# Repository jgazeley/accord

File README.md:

# Accord

Raspberry Pi Pico W firmware and keyless-entry hardware for a 2001 Honda Accord.

Two separate Pico W modules handle vehicle access and trip recording:

- **[Keyless entry](keyless/README.md)** — BLE commands, proximity-based
  lock/unlock, automatic relocking, and control of the trunk, lights and horn.
  Includes the KiCad schematic and PCB.
- **[Trip logger](logger/README.md)** — records speed/tachometer pulses,
  ignition, brake-warning and analog readings to an SD card, then uploads
  recordings over Wi-Fi during ignition-off windows.

Both run on the Pico W without an always-on in-car Linux computer. A Raspberry
Pi 4 serves as a portable development bench.

This is an ongoing vehicle-specific project. Build instructions, tests and
current limitations are documented with each module. The [logger server](logger/server/README.md) receives raw uploads and produces
trip JSON. Personal databases and dashboards are outside this repository.

## Development

This is the active home for Accord firmware, hardware and coordination.
See [current status](coordination/STATUS.md) and
[owner decisions](coordination/DECISIONS.md). Earlier experiments remain in
`accord-logger` as historical reference; useful missing material is migrated
selectively. Installed services and private data are separate from this source tree.

## License

Created by **Jayson Gazeley (jgazeley)**. Software and documentation use
[Apache 2.0](LICENSE); original hardware designs use
[CERN-OHL-P 2.0](keyless/hardware/LICENSE). Reuse, including commercial use,
is welcome with the notices required by those licenses preserved.
See [licensing and credit](LICENSING.md) for attribution and third-party terms.

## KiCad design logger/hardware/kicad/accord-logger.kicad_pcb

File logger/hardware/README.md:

# Logger hardware interface

The logger is a separate Pico W from the keyless module. The keyless KiCad
board in this repository is not a logger PCB. The current logger uses a
prototype signal-conditioning circuit, SD storage and an external regulated
5 V supply; the Pi is only a flashing and observation bench.

| Measurement/interface | Pico GPIO |
|---|---|
| Vehicle speed pulses | GP2 |
| Tachometer pulses | GP3 |
| Brake-warning level | GP4 |
| Conditioned ignition input | GP5 |
| Fuel analog input | GP26 / ADC0 |
| Supply analog input | GP27 / ADC1 |
| SD MISO / CS / SCK / MOSI | GP16 / GP17 / GP18 / GP19 |

This map comes from `accord-logger.ino` and `logger_sd.cpp`. Automotive
signals require the appropriate conditioning before reaching the Pico; this
pin map alone is not a wiring schematic. The brake-warning signal can represent
parking brake or low fluid, not an unambiguous parking-brake state. The fuel
input records ADC measurements, not an independently calibrated fuel quantity.

The **Rev A board design** is in [kicad/](kicad/) as `accord-logger.kicad_pro`:
complete schematic, 148-line BOM with every part footprinted, ERC clean, sized
for 80 × 120 mm. It includes the automatic power hold and cutoff, B2 input
isolation, the keyless RS-485 circuit, and one 10-pin Molex Mini-Fit Jr.
board connector. It is ready for the owner to place and route. It is **not
frozen and not fabrication-approved**: nothing has been built or bench tested.
The schematic is generated by `kicad/tools/gen_logger_sch.py`; see
[kicad/validation/COMMANDS.txt](kicad/validation/COMMANDS.txt). Engineering
record: [power/LAYOUT_CLOSURE.md](power/LAYOUT_CLOSURE.md); risks and bring-up
tests: [LRA12_HANDOFF.md](LRA12_HANDOFF.md). Automatic-power firmware exists
as an opt-in candidate; manual power remains the default.

The pin map above is the **as-built** firmware baseline. Rev A changes what
GP5 means and adds GP6; see [as-built/REV_A_INTERFACES.md](as-built/REV_A_INTERFACES.md) §1.

B2 input isolation (ASSR-601JV) is in the schematic; background in the
[B2 study](isolation/B2_ISOLATION.md) and [enable design](isolation/ISO_ENABLE.md).

Current electrical/PCB context: [Rev A context](REV_A_CONTEXT.md).
Current status: [STATUS.md](../../coordination/STATUS.md); owner decisions: [DECISIONS.md](../../coordination/DECISIONS.md).

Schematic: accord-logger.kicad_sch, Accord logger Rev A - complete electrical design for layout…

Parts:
BT1: BR2032; BatteryHolder_Keystone_3034_1x20mm
C1, C2: 1uF; C_0805_2012Metric_Pad1.18x1.45mm_HandSolder
C3: 1uF; C_Rect_L7.2mm_W5.5mm_P5.00mm_FKS2_FKP2_MKS2_MKP2
C4, C5, C6: 4.7uF/50V; C_1210_3225Metric_Pad1.33x2.70mm_HandSolder; MPN Murata GRM32ER71H475KA88L
C7, C17, C18, C19, C20, C21, C22, C23, C24, C25: 100nF; C_0805_2012Metric_Pad1.18x1.45mm_HandSolder
C8: 47uF/16V; CP_Radial_D6.3mm_P2.50mm
C9, C11: 100nF/100V; C_0805_2012Metric_Pad1.18x1.45mm_HandSolder
C10: 100uF/50V; CP_Radial_D8.0mm_P3.50mm; MPN Panasonic EEUFR1H101
C12: 10nF/50V; C_0805_2012Metric_Pad1.18x1.45mm_HandSolder
C13: 100nF/50V; C_0805_2012Metric_Pad1.18x1.45mm_HandSolder
C14: 1000uF/16V; CP_Radial_D10.0mm_P5.00mm; MPN Panasonic EEUFR1C102
C15: 33uF/16V; CP_Radial_Tantal_D6.0mm_P2.50mm; MPN KYOCERA AVX TAP336K016SCS
C16: 10nF; C_0805_2012Metric_Pad1.18x1.45mm_HandSolder
D101, D102, D103, D104, D105, D106, D107, D109: 1N5819; D_DO-41_SOD81_P5.08mm_Vertical_AnodeUp; MPN Diodes Inc 1N5819HW-7-F
D108, D113: 1.5KE20A-E3/54; D_DO-201AD_P5.08mm_Vertical_KathodeUp; MPN Vishay 1.5KE20A-E3/54
D110: 1N4148W; D_SOD-123; MPN Diodes Inc 1N4148W-7-F
D111: BZX55C22; D_DO-35_SOD27_P2.54mm_Vertical_KathodeUp; MPN Vishay BZX55C22-TAP
D112, D115: SB360-E3/54; D_DO-201AD_P5.08mm_Vertical_AnodeUp; MPN Vishay SB360-E3/54
D114: BZX55C10; D_DO-35_SOD27_P2.54mm_Vertical_KathodeUp; MPN Vishay BZX55C10-TAP
D116: 1N4004-E3/54; D_DO-41_SOD81_P5.08mm_Vertical_KathodeUp; MPN Vishay 1N4004-E3/54
J1: Board connector 14-way; JAE_IL-AG5-14P-D3L2-A; MPN JAE IL-AG5-14P-D3L2-A, 14 contact right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
J3: Spare GP11-13 / switched power; PinHeader_2x03_P2.54mm_Vertical
J4: Reset RUN-GND; PinHeader_1x02_P2.54mm_Vertical
J5: SD breakout 6-way; PinHeader_1x06_P2.54mm_Vertical
JP1: HOLD link; PinHeader_1x02_P2.54mm_Vertical
JP2: TERM default OPEN; PinHeader_1x02_P2.54mm_Vertical
JP3: BIAS HI default OPEN; PinHeader_1x02_P2.54mm_Vertical
JP4: BIAS LO default OPEN; PinHeader_1x02_P2.54mm_Vertical
L1: 22uH; L_Radial_D8.7mm_P5.00mm_Fastron_07HCP; MPN Bourns RLB0912-220KL
Q1, Q9: MMBT3904; SOT-23; MPN onsemi MMBT3904LT1G
Q2, Q3, Q4, Q8: BSS138P; SOT-23; MPN Nexperia BSS138P
Q5: IPD50P04P4L-11; TO-252-3_TabPin2; MPN Infineon IPD50P04P4L11ATMA2
Q6, Q7: 2N3904; TO-92_Inline; MPN onsemi 2N3904
R1, R3, R5, R10, R16: 22k; R_Axial_DIN0204_L3.6mm_D1.6mm_P5.08mm_Horizontal
R2: 33k; R_Axial_DIN0204_L3.6mm_D1.6mm_P5.08mm_Horizontal
R4, R6: 6.8k; R_Axial_DIN0204_L3.6mm_D1.6mm_P5.08mm_Horizontal
R7: 7.5k; R_Axial_DIN0204_L3.6mm_D1.6mm_P5.08mm_Horizontal
R8, R11, R18: 4.7k; R_Axial_DIN0204_L3.6mm_D1.6mm_P5.08mm_Horizontal
R9, R12, R19, R24, R26, R29, R37, R38: 1k; R_Axial_DIN0204_L3.6mm_D1.6mm_P5.08mm_Horizontal
R13: 2.2k; R_Axial_DIN0414_L11.9mm_D4.5mm_P5.08mm_Vertical
R14, R28, R44: 47k; R_Axial_DIN0204_L3.6mm_D1.6mm_P5.08mm_Horizontal
R15: 220k; R_Axial_DIN0204_L3.6mm_D1.6mm_P5.08mm_Horizontal
R17, R20, R25, R27, R34, R35: 100k; R_Axial_DIN0204_L3.6mm_D1.6mm_P5.08mm_Horizontal
R21, R31, R36: 10k; R_Axial_DIN0204_L3.6mm_D1.6mm_P5.08mm_Horizontal
R22: 820R; R_Axial_DIN0204_L3.6mm_D1.6mm_P5.08mm_Horizontal
R23: 270R; R_Axial_DIN0204_L3.6mm_D1.6mm_P5.08mm_Horizontal
R30: 10k; R_Axial_DIN0207_L6.3mm_D2.5mm_P5.08mm_Vertical
R32: 1k; R_Axial_DIN0414_L11.9mm_D4.5mm_P5.08mm_Vertical
R33: 2.2k; R_Axial_DIN0204_L3.6mm_D1.6mm_P5.08mm_Horizontal
R39: 0R; R_0805_2012Metric_Pad1.20x1.40mm_HandSolder
R40: 0R; R_0805_2012Metric_Pad1.20x1.40mm_HandSolder; not fitted
R41, R43, R45, R46: 100k; R_0805_2012Metric_Pad1.20x1.40mm_HandSolder
R42: 1k; R_0805_2012Metric_Pad1.20x1.40mm_HandSolder
R47, R48: 390R; R_Axial_DIN0207_L6.3mm_D2.5mm_P5.08mm_Vertical
R49: 120R; R_Axial_DIN0207_L6.3mm_D2.5mm_P5.08mm_Vertical
R50, R51: 4.7k; R_0805_2012Metric_Pad1.20x1.40mm_HandSolder
R52: 10k; R_0805_2012Metric_Pad1.20x1.40mm_HandSolder
TP1, TP2, TP3, TP4, TP5, TP6, TP7, TP8, TP9, TP12, TP17, TP20: TestPoint; TestPoint_Pad_D2.0mm
TP21, TP22, TP23: TestPoint; TestPoint_Loop_D2.50mm_Drill1.0mm
U1: RaspberryPi_Pico_W; RaspberryPi_Pico_W_SMD_HandSolder; MPN Raspberry Pi Pico W (RP2040 + CYW43439)
U2: PC817; DIP-4_W7.62mm; MPN Sharp PC817XNNSZ1B or qualified equival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
U3: ASSR-601JV; ASSR-601Jx_SO-16-12Lead_11.634x10.363mm_P1.27mm; MPN Broadcom ASSR-601JV-000E
U4: TPS70950QDBVRQ1; SOT-23-5_HandSoldering; MPN TI TPS70950QDBVRQ1
U5: TPS3839K50DBZR; SOT-23; MPN TI TPS3839K50DBZR
U6: LM2678T-5.0; TO-220-7_P2.54x3.7mm_StaggerOdd_Lead3.8mm_Vertical; MPN TI LM2678T-5.0/NOPB
U7: OV-7604-C7-32.768KHZ-20PPM-TA-QC; Oscillator_SMD_MicroCrystal_OV-7604-C7_SON-4_3.2x1.5mm; MPN Micro Crystal OV-7604-C7-32.768KHZ-20PP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
U8: 74AHC1G17GV; SOT-353_SC-70-5_Handsoldering; MPN Nexperia 74AHC1G17GV
U9: SN74LVC1G97DBVR; SOT-23-6_Handsoldering; MPN TI SN74LVC1G97DBVR
U10: CD74HC4060M96; SOIC-16_3.9x9.9mm_P1.27mm; MPN TI CD74HC4060M96
U11: CD74HC4020M96; SOIC-16_3.9x9.9mm_P1.27mm; MPN TI CD74HC4020M96
U12: CD4011BM96; SOIC-14_3.9x8.7mm_P1.27mm; MPN TI CD4011BM96
U13: CD4071BM96; SOIC-14_3.9x8.7mm_P1.27mm; MPN TI CD4071BM96
U14: CD4093BM96; SOIC-14_3.9x8.7mm_P1.27mm; MPN TI CD4093BM96
U15: MAX3485; DIP-8_W7.62mm; MPN Analog Devices MAX3485EPA+
U16: DS3231SN; SOIC-16W_7.5x10.3mm_P1.27mm

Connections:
/A5: C5.1, C6.1, C7.1, C18.1, C19.1, C20.1, C21.1, C22.1, C23.1, R38.1, R46.2, TP9.1, U2.4, U4.5 (OUT), U5.3 (VDD), U9.5 (VCC), U10.16 (VDD), U11.16 (VDD), U12.14 (VDD), U13.14 (VDD), U14.2 (A2), U14.14 (VDD)
/AGND: C1.2, C2.2, D105.2 (A), D107.2 (A), J1.10, R8.2, R11.2, TP23.1, U1.33 (AGND)
/ARM: R42.1, U8.2, U9.6 (IN2), U12.3 (AY), U12.6 (B2)
/ARM_G: Q8.1 (G), R42.2, R43.1
/ARM_RESET: U13.11 (DY), U14.8 (C1), U14.9 (C2)
/B1_TAP: J1.4, R3.1
/B2_ISO: R1.1, U3.9 (D2), U3.10 (D2)
/B2_TAP: J1.3, U3.15 (D1), U3.16 (D1)
/B5: C13.1, C14.1, D116.2 (A), J3.1, L1.2, R23.1, R37.1, TP5.1, U6.6 (FEEDBACK)
/B11_TAP: D108.1 (A1), D109.2 (A), J1.5, R10.1
/BAD: R16.1, U13.1 (A1), U13.8 (C1), U14.4 (BY)
/BASE_RESET: U11.11 (MR), U13.3 (AY), U13.5 (B1)
/BATT_IN: D112.2 (A), J1.6
/BOOST: C12.2, U6.3 (BOOST)
/BRAKE_IN: D103.2 (A), R5.2, R6.1, U1.6 (GPIO4)
/BUS_DE: R30.1, U1.14 (GPIO10), U15.2 (~RE), U15.3 (DE)
/C11_TAP: J1.9, R7.1
/C14_TAP: J1.13, R5.1
/CLK32: U9.4 (Y), U10.11 (CLK)
/CLKOE: U7.3 (CLKOE), U8.4
/CNT_Q8: R40.1, U11.13 (Q8)
/CNT_Q13: R39.1, U11.2 (Q13)
/COUNT1_RESET: U10.12 (MR), U13.4 (BY)
/EXPIRED: R39.2, R40.2, R41.1, U13.9 (C2)
/FAULT_RESET: U13.10 (CY), U13.12 (D1)
/FUEL_ADC: C1.1, D104.2 (A), D105.1 (K), R9.2, U1.31 (GPIO26_ADC0)
/FUEL_DIV: R7.2, R8.1, R9.1
/GATE: D114.2 (A), Q5.1 (G), R31.2, R32.1, TP2.1
/HOLD_B: Q7.2 (B), R29.2, R35.1
/HOLD_JH: JP1.2 (B), R29.1
/HOLD_N: Q9.3 (C), R46.1, U13.13 (D2)
/HOLD_RAW: JP1.1 (A), R28.1, R44.1, U1.9 (GPIO6)
/IGN_A: R14.1, R15.1, U2.3
/IGN_B: Q6.2 (B), R33.2, R34.1
/IGN_LED_A: D110.1 (K), R13.2, U2.1
/IGN_POS: D109.1 (K), R13.1, R33.1
/IGN_Q: R19.1, U12.10 (CY), U13.2 (A2), U14.12 (D1)
/IGN_RC: C3.1, R15.2, R18.2, TP12.1, U14.1 (A1)
/ISO_EN: R24.1, TP20.1, U1.10 (GPIO7)
/ISO_EN_G: Q4.1 (G), R24.2, R25.1
/ISO_LED_A: R23.2, U3.4 (AN)
/ISO_LED_K: Q3.3 (D), U3.5 (CA)
/ISO_MID: Q3.2 (S), Q4.3 (D)
/ISO_PG_G: Q3.1 (G), R26.2, R27.1
/MON_B: Q9.1 (B), R44.2, R45.1
/NARM: U12.2 (A2), U12.4 (BY), U13.6 (B2)
/P3V3_SW: C8.1, C24.1, C25.1, D101.1 (K), D102.1 (K), D103.1 (K), D104.1 (K), D106.1 (K), J3.4, J5.1, JP3.1 (A), R21.1, R50.1, R51.1, R52.1, TP7.1, U1.36 (3V3), U15.8 (VCC), U16.2 (VCC)
/P12: C9.1, D112.1 (K), D113.1 (A1), D114.1 (K), Q5.3 (S), R22.1, R31.1, TP1.1
/PGND: BT1.2 (-), C3.2, C4.2, C5.2, C6.2, C7.2, C8.2, C9.2, C10.2, C11.2, C13.2, C14.2, C15.2, C16.2, C17.2, C18.2, C19.2, C20.2, C21.2, C22.2, C23.2, C24.2, C25.2, D108.2 (A2), D110.2 (A), D111.2 (A), D113.2 (A2), D115.2 (A), J1.2, J1.14, J3.2, J4.2, J5.2, JP4.2 (B), Q1.2 (E), Q2.2 (S), Q4.2 (S), Q6.1 (E), Q7.1 (E), Q9.2 (E), R2.2, R4.2, R6.2, R14.2, R17.2, R20.2, R25.2, R27.2, R28.2, R30.2, R34.2, R35.2, R36.2, R37.2, R41.2, R43.2, R45.2, TP21.1, TP22.1, U1.3 (GND), U1.8 (GND), U1.13 (GND), U1.18 (GND), U1.23 (GND), U1.28 (GND), U1.38 (GND), U2.2, U4.2 (GND), U5.1 (GND), U6.4 (GND), U7.2 (GND), U8.3 (GND), U9.1 (IN1), U9.2 (GND), U10.8 (VSS), U11.8 (VSS), U12.7 (VSS), U12.12 (D1), U12.13 (D2), U13.7 (VSS), U14.7 (VSS), U15.5 (GND), U16.5 (GND), U16.6 (GND), U16.7 (GND), U16.8 (GND), U16.9 (GND), U16.10 (GND), U16.11 (GND), U16.12 (GND), U16.13 (GND)
/PGOOD: R26.1, TP17.1, U5.2 (~RESET), U14.5 (B1), U14.6 (B2)
/P_AON: C4.1, D111.1 (K), R22.2, TP8.1, U4.1 (IN)
/QH_C: Q7.3 (C), Q8.2 (S)
/QUAL_N: U12.8 (C1), U12.9 (C2), U14.3 (AY)
/QUAL_N_REPORT: Q2.3 (D), R21.2, U1.7 (GPIO5)
/REP_G: Q2.1 (G), R19.2, R20.1
/RESET_N: U12.5 (B1), U14.10 (CY), U14.13 (D2)
/RS485_A: J1.1, R47.2, R49.1, U15.6 (A)
/RS485_B: J1.7, JP2.2 (B), R48.1, U15.7 (B)
/RS485_BIAS_HI: JP3.2 (B), R47.1
/RS485_BIAS_LO: JP4.1 (A), R48.2
/RS485_TERM: JP2.1 (A), R49.2
/RST_B: Q1.1 (B), R16.2, R17.1
/RST_C: Q1.3 (C), R18.1
/RTC_INT: R52.2, U1.29 (GPIO22), U16.3 (~INT/SQW)
/RTC_SCL: R51.2, U1.27 (GPIO21), U16.16 (SCL)
/RTC_SDA: R50.2, U1.26 (GPIO20), U16.15 (SDA)
/RTC_VBAT: BT1.1 (+), U16.14 (VBAT)
/RUN: J4.1, U1.30 (RUN)
/SD_CS: J5.4, U1.22 (GPIO17)
/SD_MISO: J5.3, U1.21 (GPIO16)
/SD_MOSI: J5.6, U1.25 (GPIO19)
/SD_SCK: J5.5, U1.24 (GPIO18)
/SET_N: U12.1 (A1), U14.11 (DY)
/SINK: Q6.3 (C), Q8.3 (D), R32.2
/SPARE_GP11: J3.6, U1.15 (GPIO11)
/SPARE_GP12: J3.5, U1.16 (GPIO12)
/SPARE_GP13: J3.3, U1.17 (GPIO13)
/SUPPLY_ADC: C2.1, D106.2 (A), D107.1 (K), R12.2, U1.32 (GPIO27_ADC1)
/SUPPLY_DIV: R10.2, R11.1, R12.1
/SW: C12.1, D115.1 (K), L1.1, TP4.1, U6.1 (SWITCH)
/TACH_IN: D102.2 (A), R3.2, R4.1, U1.5 (GPIO3)
/UART1_RX: U1.12 (GPIO9), U15.1 (RO)
/UART1_TX: U1.11 (GPIO8), U15.4 (DI)
/UCLK_Q14: U10.3 (Q14), U11.10 (CLK)
/VCLK: C15.1, C16.1, C17.1, R38.2, U7.4 (VDD), U8.5 (VCC)
/VIN_SW: C10.1, C11.1, Q5.2 (D), R36.1, TP3.1, U6.2 (VIN)
/VSS_IN: D101.2 (A), R1.2, R2.1, U1.4 (GPIO2)
/VSYS: D116.1 (K), TP6.1, U1.39 (VSYS)
/XO_OUT: U7.1 (CLKOUT), U9.3 (IN0)

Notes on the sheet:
TEST POINTS AND GROUND LOOPS - REV_A_INTERFACES S5.3, delta D8
Onboard switched power
X6 RESOLVED: QUALIFIED IGNITION, A5 DOMAIN - CUTOFF_MARGIN_REVIEW S2
Retain 1.5KE20A by choice, not because a 60 V low-leakage QP is absent. SQD50P06-15L has 50 uA max IDSS at 125 C and -60 V. The inherited 1.5KE30A screens 43.81 V at 85 C: 1.19 V below LM2678 absolute, 3.81 V above operating. It also requires a redesigned A5 clamp. Selected 1.5KE20A screens 29.20 V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
GP0/GP1, GP14/GP15 and GP28 are deliberately unconnected. GP20/GP21 are I2C0 SDA/SCL and GP22 INT/SQW for the DS3231 (D-RTC-14). GP7 is now ISO_EN, the B2 isolation enable, confirmed free in S1. GP8/GP9 (UART1) and GP10 (tied DE//RE) drive onboard RS-485. GP13 is offered on the trimmed J3 spare/pow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
The fitted cell returned the ignition LED cathode to the B16 cluster conductor with nothing in series, putting 4.7-5.8 mA of signal- dependent current through the node both ADC channels reference, which REV_A_INTERFACES S4 says must never become a power return. D5 and that return cannot both stand.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
Pico W pin map
The opto LED return - R06-REV-2 decided
What is still open - none of it a layout blocker
Vehicle inputs: one switch, four justified bypasses
Reuses the existing power candidate as DESIGN.md S3 lists it (D-POWER-02), with the reviewed deltas D7 and D13 and the LRA-02 component selections. The LM2678, its TVS role, bulk capacitors, boost cap, inductor value and both Schottky positions all have in-service precedent on the keyless board in 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
Independent cutoff - what it does and does not cover
HOLD driver and the cutoff path
PICO W - REV_A_INTERFACES S1 Rev A column
INDEPENDENT CLOCK BLOCK - CUTOFF_MARGIN_REVIEW S1
SD and expansion
SPI0 at 12 MHz on switched 3V3 only (GP16 MISO, GP17 CS, GP18 SCK, GP19 MOSI). D6 bulk is now a selected 47 uF: a 200 mA write spike for 1 ms inside 100 mV of droop needs 2 uF, so this is an order of margin without an oversized can. Any move of this module to a 5 V rail re-opens the MISO clearance 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
RS-485 - keyless circuit; bias and termination OPEN by default
ONBOARD SWITCHED POWER - power/DESIGN.md S3, deltas D7 and D13, X7 entry clamp resolved
X7 SECOND STAGE: ALWAYS-ON A5 SUPPLY AND SUPERVISOR - CUTOFF_MARGIN_REVIEW S3 + LAYOUT_CLOSURE S3
HOLD DRIVER - delta D2
Classified in full in LRA12_HANDOFF.md. In short: ORDER GATE ASSR-601JV availability (fallback AQY221N2S specified, strictly smaller, same keepout); capacitor approval-sheet bias/aging/IR data. BRING-UP A5 ground current below 100 uA load; hot leakage of QP, QI, QH, QMON, QS, QREPORT and the opto; 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
NOTES - LRA-12 electrical closure
Test points and ground loops
IGNITION OPTO CELL, VEHICLE SIDE - AS_BUILT S3.4; LED return moved to PGND
X1 ENABLE: GPIO PLUS HARDWARE PGOOD PERMISSION - LAYOUT_CLOSURE S4
Five fitted cells, carried forward with no value changed (AS_BUILT S2). B2 is the only branch energized with the key out - 4.669 V open circuit, 4.140 V loaded, drawing 140.8 uA of which 109.2 uA was being back-fed into the unpowered 3V3 rail through a forward-biased clamp. It gets the series switc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
LRA-12 - what changed, and the one thing to read first
Nominal 2048 s from qualified ignition loss, on its own always-on supply and its own clock. The Pico cannot refresh it with HOLD, resets, network traffic or watchdog servicing; releasing HOLD disarms it, and only a qualified ignition assertion can grant it again. Reset dominates set in the settled 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
X8 RESOLVED: INDEPENDENT MAXIMUM-ON CUTOFF, 2048 s - MAX_ON_CUTOFF
GP6 HOLD_RAW with a 47k external pulldown and the JH MAINTENANCE link. Firmware latches it LOW before output enable; 4 mA drive, 2.6 V loaded qualification target. QS is the series interruption the independent timer uses: drain to SINK, source to the QH collector, body diode blocking the sink direc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
VEHICLE INPUTS - AS_BUILT S2, ratios and clamps unchanged; B2 series isolation fitted, other four branches bypassed
This is the LRA-06 capture with its eight electrical placeholders resolved. Every populated part now carries a checked footprint and no dashed NOT SELECTED body remains. The decisions, their calculations and the residual gates are in power/LAYOUT_CLOSURE.md and LRA12_HANDOFF.md; read those before c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
Twenty-five test loops. Three separate ground loops follow the keyless pattern: buck, Pico and harness end, the last on the bonded B16/AGND sense node. J4 shorts RUN to GND for a reset without cutting power. TP_PAON is where the <=28 V protected-rail criterion is measured. TP_GATE against TP_P12 is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
Voltage envelope - LRA-12R decision
SPARE GP13 / SWITCHED POWER AND RESET
SD - AS_BUILT S3.5, delta D6
REAL-TIME CLOCK - DS3231 on the board (D-RTC-14)
DS3231SN# (TCXO, -40 to +85 C) on I2C0: GP20 SDA, GP21 SCL, GP22 INT/SQW. VCC and all three pull-ups on switched 3V3 only, so nothing feeds the Pico while it is off; the chip runs from the cell then (about 3 uA). Cell: BR2032 (rated to +85 C, a parked car exceeds CR2032 ratings) in a Keystone 3034 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

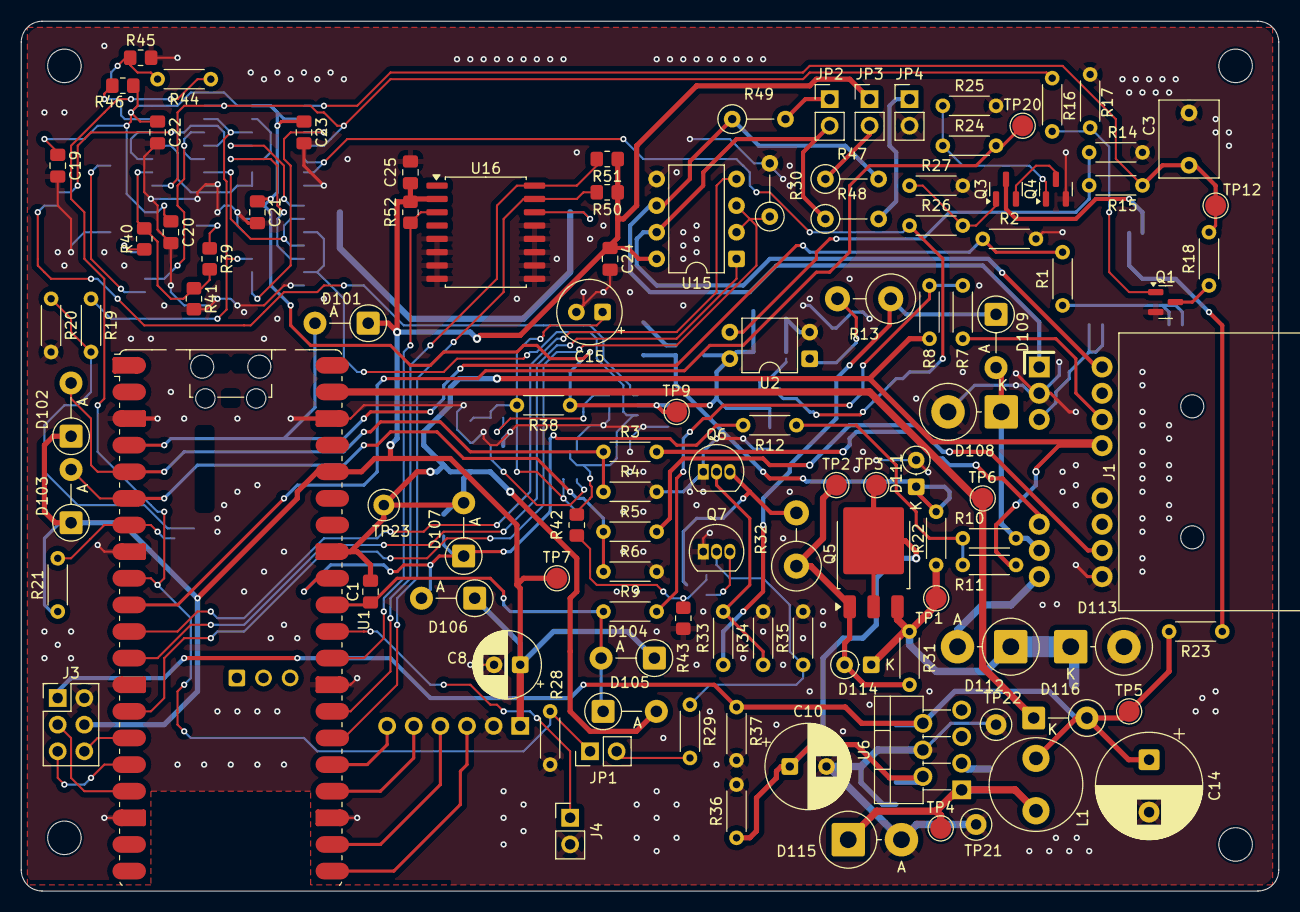
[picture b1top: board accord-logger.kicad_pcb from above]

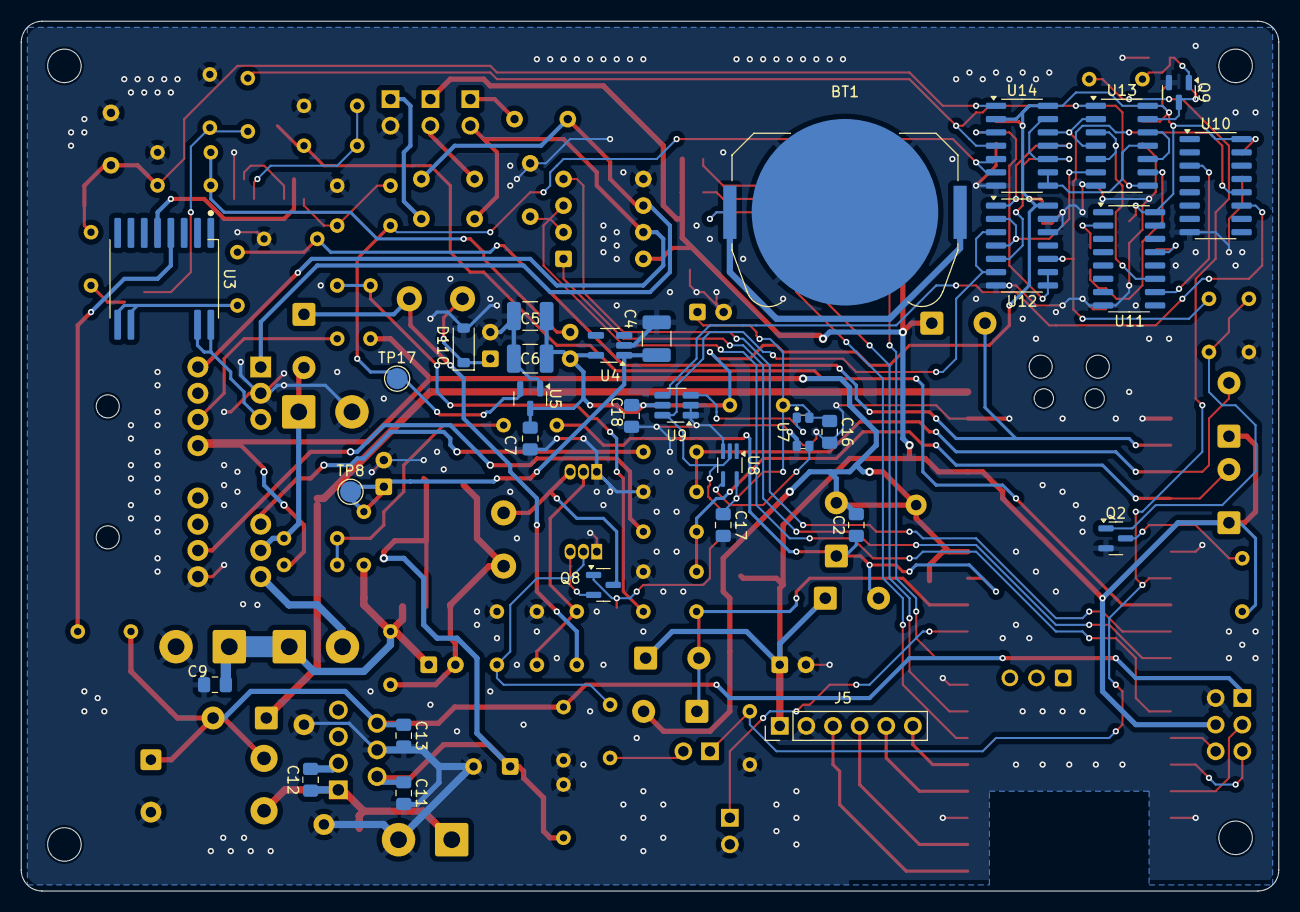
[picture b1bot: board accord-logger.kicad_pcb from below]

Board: 2 copper layers, 120.0 x 83.0 mm, 147 parts (31 on the bottom side), 89 nets.

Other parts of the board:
H1, H2, H3, H4: M3 mounting hole; MountingHole_3.2mm_M3

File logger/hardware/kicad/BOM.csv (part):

reference,source_designator,value,symbol,manufacturer_part_or_type,footprint,population,status,source,notes
J1,J1,Board connector 14-way,Connector_Generic:Conn_01x14,"JAE IL-AG5-14P-D3L2-A, 14 contact right-angle pin header",accord-logger:JAE_IL-AG5-14P-D3L2-A,FIT,SELECTED,DECISIONS D-CONN-06 / JAE IL-AG5 catalogue,"JAE IL-AG5 2.5 mm, 14 contacts, right-angle through-hole with board guides, 3 A per contact. Mates with housing IL-AG5-14S-D3C1-A and IL-AG5-C1-5000 crimp sockets (AWG 22-18); hand crimp tool CT150-1-AG5. Same family as the keyless 22P. Footprint pin numbers follow the keyless 22P convention (pin 1 outer row, left end from the mating face): verify against the housing cavity numbers before crimping. 6 BATT_IN, +12 V through the harness inline fuse (1 A, at the feed end; D-FUSE-10, no fuse on the board). 14 PGND power return; 2 PGND as the dedicated RS-485 bus ground. 10 is the B16 cluster ground sense, bonded to the single AGND node at one point (REV_A_INTERFACES S4, delta D5); never a power or bus return. 1/7 RS-485 A/B; run them as a twisted pair with pin 2. 8, 11, 12 spare"
U3,UISO,ASSR-601JV,Custom:ASSR-601JV,Broadcom ASSR-601JV-000E,accord-logger:ASSR-601Jx_SO-16-12Lead_11.634x10.363mm_P1.27mm,FIT,SELECTED_AVAILABILITY_OPEN,isolation/B2_ISOLATION.md; LAYOUT_CLOSURE S4,"B2 series isolation (D4). Output leakage 1000 nA maximum at VO = 1000 V, specified over recommended operating conditions (-40 to +105 C for the JV), against 4.669 V actually applied: the row carries no 25 C override, unlike the withstand row above it. R_ON 300 ohm max at IO = 2 mA shifts the 22k/33k ratio by -0.54 %. D1 (15, 16) and D2 (9, 10) are each internally paired and the pair is bidirectional, so orientation is free. PIN 3 MUST BE LEFT UNCONNECTED - it is internally tied to pin 5, the LED cathode. Pins 11-14 do not exist; the local footprint is a 12-pad variant derived from the manufacturer land pattern, not a stock SOIC-16W. Availability is the one open item: distributor lifecycle data is contradictory. Panasonic AQY221N2S is the documented fallback, a strictly smaller part inside the same keepout, whose 10 nA leakage maximum is 25 C only"
R1,R_VSS_T,22k,Device:R,,Resistor_THT:R_Axial_DIN0204_L3.6mm_D1.6mm_P5.08mm_Horizontal,FIT,VERIFY_STOCK,AS_BUILT S2,"fitted divider top, value unchanged; fed from the ASSR output rather than directly from the tap [D-THT-15: through-hole DIN0204, owner choice; 0.25 W metal film, 1 %.]"
R2,R_VSS_B,33k,Device:R,,Resistor_THT:R_Axial_DIN0204_L3.6mm_D1.6mm_P5.08mm_Horizontal,FIT,VERIFY_STOCK,AS_BUILT S2,"fitted divider bottom, value unchanged [D-THT-15: through-hole DIN0204, owner choice; 0.25 W metal film, 1 %.]"
D101,D_VSS,1N5819,Diode:1N5819,"1N5819 (DO-41), as fitted on the breadboard",Diode_THT:D_DO-41_SOD81_P5.08mm_Vertical_AnodeUp,FIT,VERIFY_STOCK,"AS_BUILT S2/S3.4a, U-07","fitted clamp, anode at the pin, cathode to switched 3V3. This is the specimen behind U-07's first measured point: the parked B2 readings give it 159 mV at 109 uA at room temperature, a Schottky drop. With UISO fitted the branch is open upstream when the board is off, so this clamp no longer has a parked path to conduct [D-THT-15: back to the through-hole 1N5819 on DO-41 vertical; pad 1 is the cathode, as before.]"
R3,R_TACH_T,22k,Device:R,,Resistor_THT:R_Axial_DIN0204_L3.6mm_D1.6mm_P5.08mm_Horizontal,FIT,VERIFY_STOCK,AS_BUILT S2,"fitted divider top, value unchanged. D4 bypass, decided in LAYOUT_CLOSURE S4: this branch is ignition-fed and measured or logged dead with the key out, so criterion A is met with no device at all. Reaching criterion B needs the key on AND an upstream power fault, because ignition present turns QI on and powers the board. In that fault state the fitted series resistance bounds the injection. [D-THT-15: through-hole DIN0204, owner choice; 0.25 W metal film, 1 %.]"
R4,R_TACH_B,6.8k,Device:R,,Resistor_THT:R_Axial_DIN0204_L3.6mm_D1.6mm_P5.08mm_Horizontal,FIT,VERIFY_STOCK,AS_BUILT S2,"fitted divider bottom, value unchanged [D-THT-15: through-hole DIN0204, owner choice; 0.25 W metal film, 1 %.]"
D102,D_TACH,1N5819,Diode:1N5819,"1N5819 (DO-41), as fitted on the breadboard",Diode_THT:D_DO-41_SOD81_P5.08mm_Vertical_AnodeUp,FIT,VERIFY_STOCK,"AS_BUILT S2/S3.4a, U-07","fitted clamp, anode at the pin, cathode to switched 3V3. D11 remains open for the tach cell: V_F keeps falling below 109 uA, so its clamp onset is lower than a 0.3 V assumption gives. LRA-12 changes no ratio [D-THT-15: back to the through-hole 1N5819 on DO-41 vertical; pad 1 is the cathode, as before.]"
R5,R_BRK_T,22k,Device:R,,Resistor_THT:R_Axial_DIN0204_L3.6mm_D1.6mm_P5.08mm_Horizontal,FIT,VERIFY_STOCK,AS_BUILT S2,"fitted divider top, value unchanged. D4 bypass, decided in LAYOUT_CLOSURE S4: this branch is ignition-fed and measured or logged dead with the key out, so criterion A is met with no device at all. Reaching criterion B needs the key on AND an upstream power fault, because ignition present turns QI on and powers the board. In that fault state the fitted series resistance bounds the injection. [D-THT-15: through-hole DIN0204, owner choice; 0.25 W metal film, 1 %.]"
R6,R_BRK_B,6.8k,Device:R,,Resistor_THT:R_Axial_DIN0204_L3.6mm_D1.6mm_P5.08mm_Horizontal,FIT,VERIFY_STOCK,AS_BUILT S2,"fitted divider bottom, value unchanged [D-THT-15: through-hole DIN0204, owner choice; 0.25 W metal film, 1 %.]"
D103,D_BRK,1N5819,Diode:1N5819,"1N5819 (DO-41), as fitted on the breadboard",Diode_THT:D_DO-41_SOD81_P5.08mm_Vertical_AnodeUp,FIT,VERIFY_STOCK,"AS_BUILT S2/S3.4a, U-07","fitted clamp, anode at the pin, cathode to switched 3V3. D11 remains open for the tach cell: V_F keeps falling below 109 uA, so its clamp onset is lower than a 0.3 V assumption gives. LRA-12 changes no ratio [D-THT-15: back to the through-hole 1N5819 on DO-41 vertical; pad 1 is the cathode, as before.]"
R7,R_FUEL_T,7.5k,Device:R,,Resistor_THT:R_Axial_DIN0204_L3.6mm_D1.6mm_P5.08mm_Horizontal,FIT,VERIFY_STOCK,AS_BUILT S2,"fitted divider top, value unchanged. D4 bypass, decided in LAYOUT_CLOSURE S4: this branch is ignition-fed and measured or logged dead with the key out, so criterion A is met with no device at all. Reaching criterion B needs the key on AND an upstream power fault, because ignition present turns QI on and powers the board. In that fault state the fitted series resistance bounds the injection. No series element is added, so the card header's two-term fuel calibration (log.adc.fuel div=7500/4700) stays valid and REV_A_INTERFACES S8.2 needs no change [D-THT-15: through-hole DIN0204, owner choice; 0.25 W metal film, 1 %.]"
R8,R_FUEL_B,4.7k,Device:R,,Resistor_THT:R_Axial_DIN0204_L3.6mm_D1.6mm_P5.08mm_Horizontal,FIT,VERIFY_STOCK,AS_BUILT S2/S3.3,"fitted divider bottom; returns to the single B16 sense node [D-THT-15: through-hole DIN0204, owner choice; 0.25 W metal film, 1 %.]"
R9,R_FUEL_S,1k,Device:R,,Resistor_THT:R_Axial_DIN0204_L3.6mm_D1.6mm_P5.08mm_Horizontal,FIT,VERIFY_STOCK,AS_BUILT S2 rows 4a/5a,"fitted series resistor at the pin [D-THT-15: through-hole DIN0204, owner choice; 0.25 W metal film, 1 %.]"
C1,C_FUEL,1uF,Device:C,,Capacitor_SMD:C_0805_2012Metric_Pad1.18x1.45mm_HandSolder,FIT,VERIFY_OR_SOURCE,AS_BUILT S2 rows 4a/5a,"fitted filter capacitor; exact dielectric/rating not recorded [D-SMD-09: 0805 X7R, rated voltage not below the disc it replaces]"
D104,D_FUEL_H,1N5819,Diode:1N5819,"1N5819 (DO-41), as fitted on the breadboard",Diode_THT:D_DO-41_SOD81_P5.08mm_Vertical_AnodeUp,FIT,VERIFY_STOCK,AS_BUILT S2 rows 4a/5a,"fitted upper clamp [D-THT-15: back to the through-hole 1N5819 on DO-41 vertical; pad 1 is the cathode, as before.]"
D105,D_FUEL_L,1N5819,Diode:1N5819,"1N5819 (DO-41), as fitted on the breadboard",Diode_THT:D_DO-41_SOD81_P5.08mm_Vertical_AnodeUp,FIT,VERIFY_STOCK,AS_BUILT S2 rows 4a/5a,"fitted lower clamp [D-THT-15: back to the through-hole 1N5819 on DO-41 vertical; pad 1 is the cathode, as before.]"
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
